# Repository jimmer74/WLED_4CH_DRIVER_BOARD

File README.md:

# 4 Channel WS2812B WLED driver

## Disclaimer/Licence

This project (4 Channel WS2812B WLED driver - henceforth know as "The Project") is dual licenced.

If you want to use The Project for your own personal purposes (i.e. for your own use, not for financial/commercial gain), then please feel free to use and modify it as needed. No warrentee is given and no liability is assumed by me.

If you wish to use The Project, or any aspect of it, commercially please seek my permission.  I DO NOT give consent for any of the work in The Project to be used for commercial gain by others unless with my express agreement. If terms can be agreed commercially, consent will be provided by me in writing. If you do not have such consent in writing from me, you do not have the right to use The Project, or any aspect of it, commercially.

## What is this?

I wanted a custom WS2812B board, capable of driving up to 4 strips.

I have some decent Meanwell +5v high-current PSUs on hand, and this board is designed to be fed by something like that. There's a distinct lack of overcurrent protection (apart from the obvious 5mmx20mm fuse for whole board and a 5A LF resettable fuse/channel) and I'm relying on a well-made and well-specced power supply for the rest. There's no reverse voltage protection, for instance, but the PWR_IN connector is clearly marked which end is which!

A custom build of WLED including the multirelay usermod will be needed, to make this board work. I'll probably get round to updating this readme with instructions/config at some point.

If you make up a jst-xh 1x5 connector and wire it to a INMP441 microphone off-board somewhere, then you can activate the Audioreactive usermod and enjoy some beats-driven lighting.

## Board 3d Render

## PCB Layout

## Schematic

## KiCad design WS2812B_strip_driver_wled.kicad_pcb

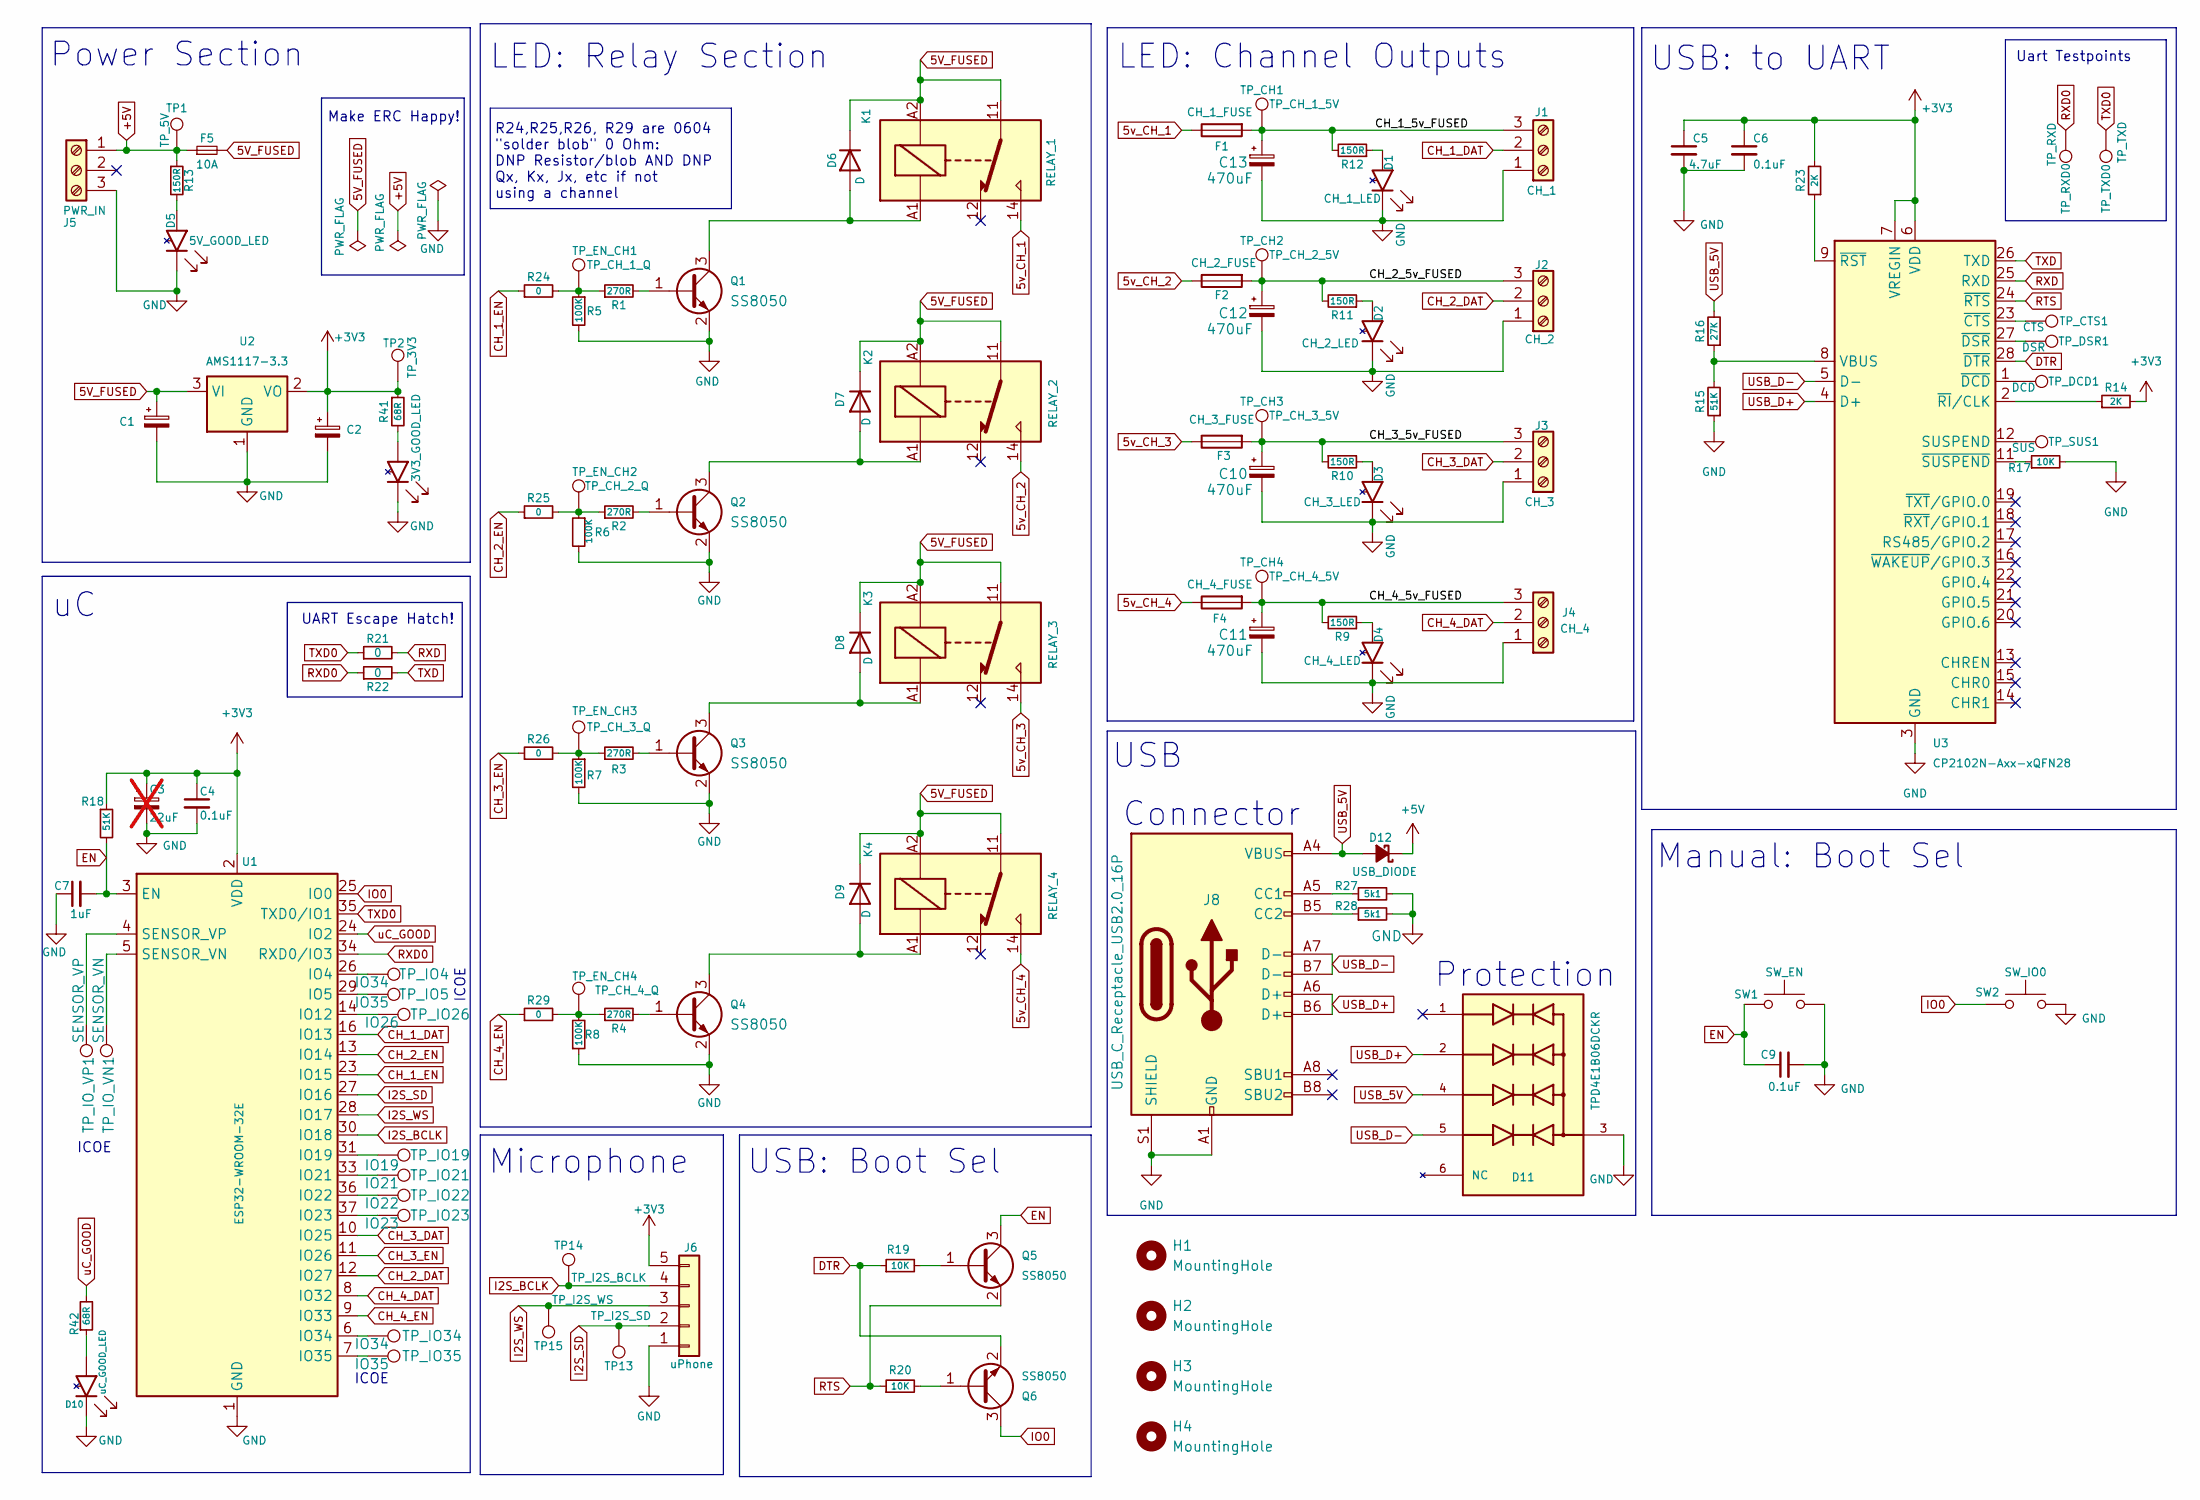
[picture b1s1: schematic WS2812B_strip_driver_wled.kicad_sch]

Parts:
C1, C2: 22uF; CP_Radial_D4.0mm_P2.00mm
C3: 22uF; CP_Radial_D4.0mm_P2.00mm; not fitted
C4, C6, C9: 0.1uF; C_0805_2012Metric
C5: 4.7uF; C_0805_2012Metric
C7: 1uF; C_0805_2012Metric
C10, C11, C12, C13: 470uF; CP_Radial_D8.0mm_P5.00mm
D1: CH_1_LED; LED_Single_SOT23_Lumex
D2: CH_2_LED; LED_Single_SOT23_Lumex
D3: CH_3_LED; LED_Single_SOT23_Lumex
D4: CH_4_LED; LED_Single_SOT23_Lumex
D5: 5V_GOOD_LED; LED_Single_SOT23_Lumex
D6, D7, D8, D9: D; D_SMC
D10: uC_GOOD_LED; LED_Single_SOT23_Lumex
D11: TPD4E1B06DCKR; TVS_TPD4E1B06DCKR
D12: USB_DIODE; Nexperia_CFP3_SOD-123W
D13: 3V3_GOOD_LED; LED_Single_SOT23_Lumex
F1: CH_1_FUSE; Fuse_2920_7451Metric
F2: CH_2_FUSE; Fuse_2920_7451Metric
F3: CH_3_FUSE; Fuse_2920_7451Metric
F4: CH_4_FUSE; Fuse_2920_7451Metric
F5: 10A; Wurth_696_Fuseholder
H1, H2, H3, H4: MountingHole; MountingHole_3.2mm_M3
J1: CH_1; TerminalBlock_Phoenix_MKDS-1,5-3-5.08_1x03_P5.08mm_Horizont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
J2: CH_2; TerminalBlock_Phoenix_MKDS-1,5-3-5.08_1x03_P5.08mm_Horizont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
J3: CH_3; TerminalBlock_Phoenix_MKDS-1,5-3-5.08_1x03_P5.08mm_Horizont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
J4: CH_4; TerminalBlock_Phoenix_MKDS-1,5-3-5.08_1x03_P5.08mm_Horizont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
J5: PWR_IN; TerminalBlock_Phoenix_MKDS-1,5-3-5.08_1x03_P5.08mm_Horizont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
J6: uPhone; JST_XH_S5B-XH-A-1_1x05_P2.50mm_Horizontal
J8: USB_C_Receptacle_USB2.0_16P; USB_C_Receptacle_HRO_TYPE-C-31-M-12
K1: RELAY_1; Relay_SPDT_Hongfa_JQC-3FF_0XX-1Z
K2: RELAY_2; Relay_SPDT_Hongfa_JQC-3FF_0XX-1Z
K3: RELAY_3; Relay_SPDT_Hongfa_JQC-3FF_0XX-1Z
K4: RELAY_4; Relay_SPDT_Hongfa_JQC-3FF_0XX-1Z
Q1, Q2, Q3, Q4, Q5, Q6: SS8050; SOT-23
R1, R2, R3, R4: 270R; R_0805_2012Metric
R5, R6, R7, R8: 100K; R_0805_2012Metric
R9, R10, R11, R12, R13: 150R; R_0805_2012Metric
R14, R23: 2K; R_0805_2012Metric
R15, R18: 51K; R_0805_2012Metric
R16: 27K; R_0805_2012Metric
R17, R19, R20: 10K; R_0805_2012Metric
R21, R22: 0; R_0805_2012Metric
R24, R25, R26, R29: 0; R_0402_1005Metric
R27, R28: 5k1; R_0805_2012Metric
R41, R42: 68R; R_0805_2012Metric
SW1: SW_EN; SW_SPST_PTS645
SW2: SW_IO0; SW_SPST_PTS645
TP1: TP_5V; TestPoint_Pad_2.0x2.0mm
TP2: TP_3V3; TestPoint_Pad_2.0x2.0mm
TP13: TP_I2S_SD; TESTPOINT_SMD_HARWIN_EZ_BOARDWARE_3.45X1.85mm
TP14: TP_I2S_BCLK; TESTPOINT_SMD_HARWIN_EZ_BOARDWARE_3.45X1.85mm
TP15: TP_I2S_WS; TESTPOINT_SMD_HARWIN_EZ_BOARDWARE_3.45X1.85mm
TP_CH1: TP_CH_1_5V; TestPoint_Pad_2.0x2.0mm
TP_CH2: TP_CH_2_5V; TestPoint_Pad_2.0x2.0mm
TP_CH3: TP_CH_3_5V; TestPoint_Pad_2.0x2.0mm
TP_CH4: TP_CH_4_5V; TestPoint_Pad_2.0x2.0mm
TP_CTS1: CTS; TestPoint_Pad_1.0x1.0mm
TP_DCD1: DCD; TestPoint_Pad_1.0x1.0mm
TP_DSR1: DSR; TestPoint_Pad_1.0x1.0mm
TP_EN_CH1: TP_CH_1_Q; TESTPOINT_SMD_HARWIN_EZ_BOARDWARE_3.45X1.85mm
TP_EN_CH2: TP_CH_2_Q; TESTPOINT_SMD_HARWIN_EZ_BOARDWARE_3.45X1.85mm
TP_EN_CH3: TP_CH_3_Q; TESTPOINT_SMD_HARWIN_EZ_BOARDWARE_3.45X1.85mm
TP_EN_CH4: TP_CH_4_Q; TESTPOINT_SMD_HARWIN_EZ_BOARDWARE_3.45X1.85mm
TP_IO4, TP_IO34: IO34; TestPoint_Pad_1.0x1.0mm
TP_IO5, TP_IO35: IO35; TestPoint_Pad_1.0x1.0mm
TP_IO19: IO19; TestPoint_Pad_1.0x1.0mm
TP_IO21: IO21; TestPoint_Pad_1.0x1.0mm
TP_IO22: IO22; TestPoint_Pad_1.0x1.0mm
TP_IO23: IO23; TestPoint_Pad_1.0x1.0mm
TP_IO26: IO26; TestPoint_Pad_1.0x1.0mm
TP_IO_VN1: SENSOR_VN; TestPoint_Pad_1.0x1.0mm
TP_IO_VP1: SENSOR_VP; TestPoint_Pad_1.0x1.0mm
TP_RXD0: TP_RXD; TESTPOINT_SMD_HARWIN_EZ_BOARDWARE_3.45X1.85mm
TP_SUS1: SUS; TestPoint_Pad_1.0x1.0mm
TP_TXD0: TP_TXD; TESTPOINT_SMD_HARWIN_EZ_BOARDWARE_3.45X1.85mm
U1: ESP32-WROOM-32E; ESP32-WROOM-32E-0.3VIAS
U2: AMS1117-3.3; SOT-223-3_TabPin2
U3: CP2102N-Axx-xQFN28; QFN-28-1EP_5x5mm_P0.5mm_EP3.35x3.35mm

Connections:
5V_FUSED: C1.1, D6.1 (K), D7.1 (K), D8.1 (K), D9.1 (K), F5.2, K1.11, K1.A2, K2.11, K2.A2, K3.11, K3.A2, K4.11, K4.A2, U2.3 (VI)
5v_CH_1: F1.1, K1.14
5v_CH_2: F2.1, K2.14
5v_CH_3: F3.1, K3.14
5v_CH_4: F4.1, K4.14
+3V3: C2.1, C3.1, C4.1, C5.1, C6.1, J6.5, R14.2, R18.1, R23.2, R41.1, TP2.1, U1.2 (VDD), U2.2 (VO), U3.6 (VDD), U3.7 (VREGIN)
+5V: D12.1 (K), F5.1, J5.1, R13.1, TP1.1
/CH_1_5v_FUSED: C13.1, F1.2, J1.3, R12.2, TP_CH1.1
/CH_2_5v_FUSED: C12.1, F2.2, J2.3, R11.2, TP_CH2.1
/CH_3_5v_FUSED: C10.1, F3.2, J3.3, R10.1, TP_CH3.1
/CH_4_5v_FUSED: C11.1, F4.2, J4.3, R9.2, TP_CH4.1
CH_1_DAT: J1.2, U1.16 (IO13)
CH_1_EN: R24.1, U1.23 (IO15)
CH_2_DAT: J2.2, U1.12 (IO27)
CH_2_EN: R25.1, U1.13 (IO14)
CH_3_DAT: J3.2, U1.10 (IO25)
CH_3_EN: R26.1, U1.11 (IO26)
CH_4_DAT: J4.2, U1.8 (IO32)
CH_4_EN: R29.1, U1.9 (IO33)
DTR: Q6.2 (E), R19.1, U3.28 (~DTR)
EN: C7.2, C9.1, Q5.3 (C), R18.2, SW1.1, U1.3 (EN)
GND: C1.2, C2.2, C3.2, C4.2, C5.2, C6.2, C7.1, C9.2, C10.2, C11.2, C12.2, C13.2, D1.3, D2.3, D3.3, D4.3, D5.3, D10.3, D11.3, D13.3, J1.1, J2.1, J3.1, J4.1, J5.3, J6.1, J8.A1 (GND), J8.A12 (GND), J8.B1 (GND), J8.B12 (GND), J8.S1 (SHIELD), Q1.2 (E), Q2.2 (E), Q3.2 (E), Q4.2 (E), R5.2, R6.2, R7.2, R8.1, R15.1, R17.2, R27.2, R28.2, SW1.2, SW2.2, U1.1 (GND), U1.15 (GND), U1.38 (GND), U1.39 (GND), U2.1 (GND), U3.3 (GND), U3.29 (GND)
I2S_BCLK: J6.4, TP14.1, U1.30 (IO18)
I2S_SD: J6.2, TP13.1, U1.27 (IO16)
I2S_WS: J6.3, TP15.1, U1.28 (IO17)
IO0: Q6.3 (C), SW2.1, U1.25 (IO0)
unnamed: D1.2, R12.1
unnamed: D2.2, R11.1
unnamed: D3.2, R10.2
unnamed: D4.2, R9.1
unnamed: D5.2, R13.2
unnamed: D6.2 (A), K1.A1, Q1.3 (C)
unnamed: D7.2 (A), K2.A1, Q2.3 (C)
unnamed: D8.2 (A), K3.A1, Q3.3 (C)
unnamed: D9.2 (A), K4.A1, Q4.3 (C)
unnamed: D10.2, R42.1
unnamed: D13.2, R41.2
unnamed: J8.A5 (CC1), R27.1
unnamed: J8.B5 (CC2), R28.1
unnamed: Q1.1 (B), R1.2
unnamed: Q2.1 (B), R2.2
unnamed: Q3.1 (B), R3.2
unnamed: Q4.1 (B), R4.2
unnamed: Q5.1 (B), R19.2
unnamed: Q6.1 (B), R20.2
unnamed: R1.1, R5.1, R24.2, TP_EN_CH1.1
unnamed: R2.1, R6.1, R25.2, TP_EN_CH2.1
unnamed: R3.1, R7.1, R26.2, TP_EN_CH3.1
unnamed: R4.1, R8.2, R29.2, TP_EN_CH4.1
unnamed: TP_IO4.1, U1.26 (IO4)
unnamed: TP_IO5.1, U1.29 (IO5)
unnamed: TP_IO26.1, U1.14 (IO12)
unnamed: TP_IO19.1, U1.31 (IO19)
unnamed: TP_IO21.1, U1.33 (IO21)
unnamed: TP_IO22.1, U1.36 (IO22)
unnamed: TP_IO23.1, U1.37 (IO23)
unnamed: TP_IO34.1, U1.6 (IO34)
unnamed: TP_IO35.1, U1.7 (IO35)
unnamed: TP_IO_VN1.1, U1.5 (SENSOR_VN)
unnamed: TP_IO_VP1.1, U1.4 (SENSOR_VP)
unnamed: TP_SUS1.1, U3.12 (SUSPEND)
unnamed: R15.2, R16.1, U3.8 (VBUS)
unnamed: TP_CTS1.1, U3.23 (~CTS)
unnamed: TP_DCD1.1, U3.1 (~DCD)
unnamed: TP_DSR1.1, U3.27 (~DSR)
unnamed: R14.1, U3.2 (~RI/CLK)
unnamed: R23.1, U3.9 (~RST)
unnamed: R17.1, U3.11 (~SUSPEND)
RTS: Q5.2 (E), R20.1, U3.24 (~RTS)
RXD: R21.2, U3.25 (RXD)
RXD0: R22.1, TP_RXD0.1, U1.34 (RXD0/IO3)
TXD: R22.2, U3.26 (TXD)
TXD0: R21.1, TP_TXD0.1, U1.35 (TXD0/IO1)
USB_5V: D11.4, D12.2 (A), J8.A4 (VBUS), J8.A9 (VBUS), J8.B4 (VBUS), J8.B9 (VBUS), R16.2
USB_D+: D11.2, J8.A6 (D+), J8.B6 (D+), U3.4 (D+)
USB_D-: D11.5, J8.A7 (D-), J8.B7 (D-), U3.5 (D-)
uC_GOOD: R42.2, U1.24 (IO2)

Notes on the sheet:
Protection
Connector
Uart Testpoints
ICOE
USB
R24,R25,R26, R29 are 0604 "solder blob" 0 Ohm: DNP Resistor/blob AND DNP Qx, Kx, Jx, etc if not using a channel
Manual: Boot Sel
Make ERC Happy!
Power Section
UART Escape Hatch!
Microphone
LED: Channel Outputs
LED: Relay Section
USB: to UART
USB: Boot Sel

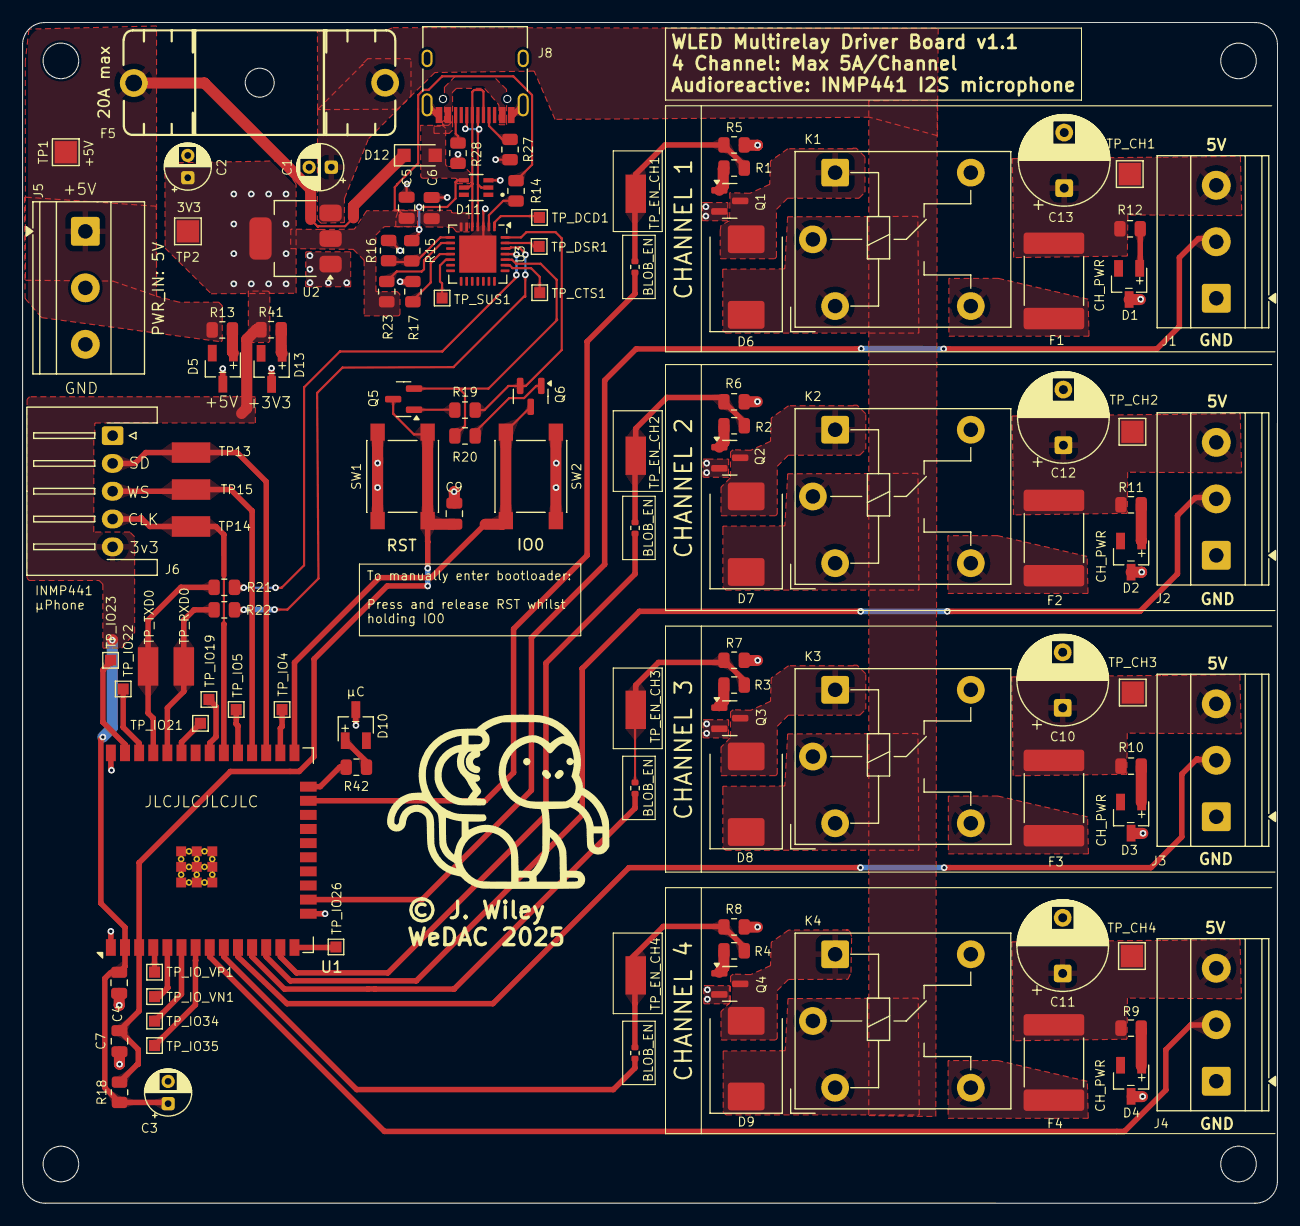
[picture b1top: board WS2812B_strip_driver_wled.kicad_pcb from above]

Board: 2 copper layers, 112.9 x 106.2 mm, 117 parts (0 on the bottom side), 77 nets.

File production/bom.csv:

Designator,Footprint,Quantity,Value,LCSC Part #
"C1, C2",CP_Radial_D4.0mm_P2.00mm,2,22uF,
"C10, C11, C12, C13",CP_Radial_D8.0mm_P5.00mm,4,470uF,
"C4, C6, C7, C8, C9",0805,5,0.1uF,
C5,0805,1,4.7uF,
D1,LED_Single_SOT23_Lumex,1,CH_1_LED,
D10,LED_Single_SOT23_Lumex,1,uC_GOOD_LED,
D11,TVS_TPD4E1B06DCKR,1,TPD4E1B06DCKR,
D12,Nexperia_CFP3_SOD-123W,1,USB_DIODE,
D13,LED_Single_SOT23_Lumex,1,3V3_GOOD_LED,
D2,LED_Single_SOT23_Lumex,1,CH_2_LED,
D3,LED_Single_SOT23_Lumex,1,CH_3_LED,
D4,LED_Single_SOT23_Lumex,1,CH_4_LED,
D5,LED_Single_SOT23_Lumex,1,5V_GOOD_LED,
"D6, D7, D8, D9",D_SMC,4,D,
F1,2920,1,CH_1_FUSE,
F2,2920,1,CH_2_FUSE,
F3,2920,1,CH_3_FUSE,
F4,2920,1,CH_4_FUSE,
F5,Wurth_696_Fuseholder,1,10A,
J1,"TerminalBlock_Phoenix_MKDS-1,5-3-5.08_1x03_P5.08mm_Horizontal",1,CH_1,
J2,"TerminalBlock_Phoenix_MKDS-1,5-3-5.08_1x03_P5.08mm_Horizontal",1,CH_2,
J3,"TerminalBlock_Phoenix_MKDS-1,5-3-5.08_1x03_P5.08mm_Horizontal",1,CH_3,
J4,"TerminalBlock_Phoenix_MKDS-1,5-3-5.08_1x03_P5.08mm_Horizontal",1,CH_4,
J5,"TerminalBlock_Phoenix_MKDS-1,5-3-5.08_1x03_P5.08mm_Horizontal",1,PWR_IN,
J6,JST_XH_S5B-XH-A-1_1x05_P2.50mm_Horizontal,1,uPhone,
J8,USB_C_Receptacle_HRO_TYPE-C-31-M-12,1,USB_C_Receptacle_USB2.0_16P,
K1,Relay_SPDT_Hongfa_JQC-3FF_0XX-1Z,1,RELAY_1,
K2,Relay_SPDT_Hongfa_JQC-3FF_0XX-1Z,1,RELAY_2,
K3,Relay_SPDT_Hongfa_JQC-3FF_0XX-1Z,1,RELAY_3,
K4,Relay_SPDT_Hongfa_JQC-3FF_0XX-1Z,1,RELAY_4,
"Q1, Q2, Q3, Q4, Q5, Q6",SOT-23,6,SS8050,
"R1, R2, R3, R4",0805,4,220,
"R10, R42, R9",0805,3,170R,
"R11, R12, R13, R41",0805,4,170,
"R14, R23",0805,2,2K,
R15,0805,1,47K5,
R16,0805,1,22K1,
"R17, R18, R19, R20",0805,4,10K,
"R21, R22",0805,2,0,
"R24, R25, R26, R29",0402,4,0,
"R27, R28",0805,2,5k1,
"R5, R6, R7, R8",0805,4,100K,
SW1,SW_SPST_PTS645,1,SW_EN,
SW2,SW_SPST_PTS645,1,SW_IO0,
TP1,TestPoint_Pad_2.0x2.0mm,1,TP_5V,
TP13,TESTPOINT_SMD_HARWIN_EZ_BOARDWARE_3.45X1.85mm,1,TP_I2S_SD,
TP14,TESTPOINT_SMD_HARWIN_EZ_BOARDWARE_3.45X1.85mm,1,TP_I2S_BCLK,
TP15,TESTPOINT_SMD_HARWIN_EZ_BOARDWARE_3.45X1.85mm,1,TP_I2S_WS,
TP2,TestPoint_Pad_2.0x2.0mm,1,TP_3V3,
TP_CH1,TestPoint_Pad_2.0x2.0mm,1,TP_CH_1_5V,
TP_CH2,TestPoint_Pad_2.0x2.0mm,1,TP_CH_2_5V,
TP_CH3,TestPoint_Pad_2.0x2.0mm,1,TP_CH_3_5V,
TP_CH4,TestPoint_Pad_2.0x2.0mm,1,TP_CH_4_5V,
TP_CTS1,TestPoint_Pad_1.0x1.0mm,1,CTS,
TP_DCD1,TestPoint_Pad_1.0x1.0mm,1,DCD,
TP_DSR1,TestPoint_Pad_1.0x1.0mm,1,DSR,
TP_EN_CH1,TESTPOINT_SMD_HARWIN_EZ_BOARDWARE_3.45X1.85mm,1,TP_CH_1_Q,
TP_EN_CH2,TESTPOINT_SMD_HARWIN_EZ_BOARDWARE_3.45X1.85mm,1,TP_CH_2_Q,
TP_EN_CH3,TESTPOINT_SMD_HARWIN_EZ_BOARDWARE_3.45X1.85mm,1,TP_CH_3_Q,
TP_EN_CH4,TESTPOINT_SMD_HARWIN_EZ_BOARDWARE_3.45X1.85mm,1,TP_CH_4_Q,
TP_IO19,TestPoint_Pad_1.0x1.0mm,1,IO19,
TP_IO21,TestPoint_Pad_1.0x1.0mm,1,IO21,
TP_IO22,TestPoint_Pad_1.0x1.0mm,1,IO22,
TP_IO23,TestPoint_Pad_1.0x1.0mm,1,IO23,
TP_IO26,TestPoint_Pad_1.0x1.0mm,1,IO26,
"TP_IO34, TP_IO4",TestPoint_Pad_1.0x1.0mm,2,IO34,
"TP_IO35, TP_IO5",TestPoint_Pad_1.0x1.0mm,2,IO35,
TP_IO_VN1,TestPoint_Pad_1.0x1.0mm,1,SENSOR_VN,
TP_IO_VP1,TestPoint_Pad_1.0x1.0mm,1,SENSOR_VP,
TP_RXD0,TESTPOINT_SMD_HARWIN_EZ_BOARDWARE_3.45X1.85mm,1,TP_RXD,
TP_SUS1,TestPoint_Pad_1.0x1.0mm,1,SUS,
TP_TXD0,TESTPOINT_SMD_HARWIN_EZ_BOARDWARE_3.45X1.85mm,1,TP_TXD,
U1,ESP32-WROOM-32E,1,ESP32-WROOM-32E,
U2,SOT-223-3_TabPin2,1,AMS1117-3.3,
U3,QFN-28-1EP_5x5mm_P0.5mm_EP3.35x3.35mm,1,CP2102N-Axx-xQFN28,

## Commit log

2025-06-15 better gitignore
2025-06-15 added btn labels, moved logo
2025-06-15 More silkscreen improvements/additions
2025-06-15 reordered channels, renamed TP's, moved uC good led
2025-06-15 added 0402 zero-ohm for solder-blob jumpering the channels. Even better silkscreen
2025-06-15 added JLCJLCJLCJLC to silkscreen for manual positioning under chip
2025-06-16 more silkscreen updates, moved pwr_in connnector slightly to allow room for better labelling
2025-06-16 removed backups from git
2025-06-16 removed cache from git
2025-06-16 moved testpoints, aligned channel 1, better silkscreen
2025-06-16 created v1.0 gerbers
2025-06-17 removed micro vias by usb-c connection
2025-06-17 created v1.1 gerbers
2025-06-17 cleaned up schematic. assigned esp32e as my custom version with 0.3mm vias to stop drc warnings
2025-06-17 updated readme with licence info, brief description and some images
2025-06-17 correctly included the README images
2025-06-25 swapped incorrect rx/tx pins
2025-06-25 swapped change en rc circuit vals, removed io btn debouncing cap. Board now fires straight up

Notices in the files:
WS2812B_strip_driver_wled.kicad_pcb:
© J. Wiley
